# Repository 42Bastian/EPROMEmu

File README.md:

# LynxCartEmu

This repo is based on Brian's repo, see original comments below.

This fork is solely to support Atari Lynx Carts.
Upon start, the firmware loads either a `game.lnx` file or if not available provides a uBLL for Lynx.

A new ROM image can be uploaded (as .lnx file) and will be stored in internal RAM and on SD card (if available) for the next boot.

Sending is done via `SendCard.py`.

The firmware allows to "reload" the SD cart via serial command `cr` if game.lnx was saved on a PC on the card.

---

# EPROMEmu

**!! WARNING: I have no idea what I'm doing !!**

I've decided to make this public in the rare event it might help someone.

This is a very simple, likely very wrong (EP)ROM emulator using a Teensy 4.1 and Arduino/PlatformIO.  It works for my purposes (emulating an EPROM for
use in an Atari Lynx EPROM cartridge), but it it is probably not the "correct" way to design hardware.  I have also used it on Game Gear and Vectrex EPROM cartridges,
but it was not heavily tested.

Please take caution with using anything you see here.  It's my first time using KiCad, my first time designing a PCB, and my first time creating hardware.  Again,
it works for my purposes, but perhaps it'll burn your house down.

Enjoy!

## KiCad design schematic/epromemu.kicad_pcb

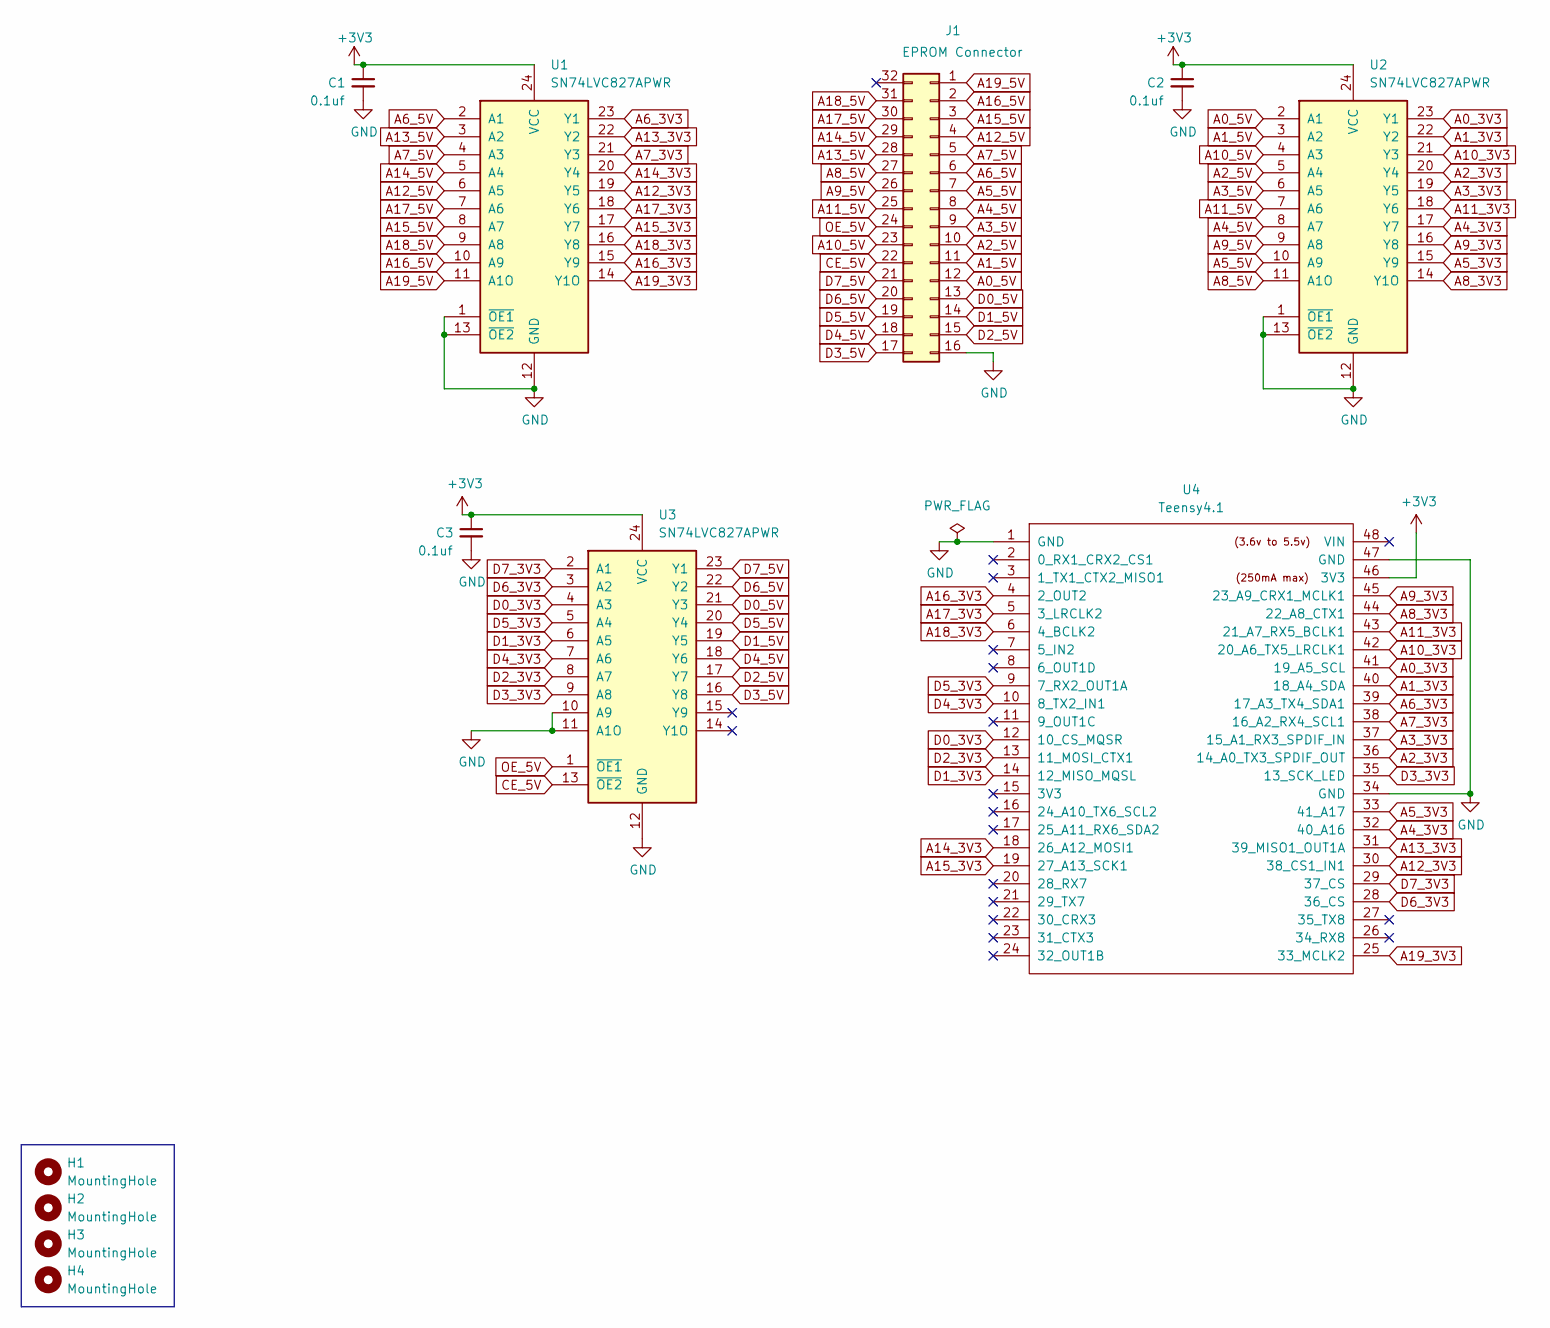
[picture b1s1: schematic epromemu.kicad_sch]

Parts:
C1, C2, C3: 0.1uf; C_0603_1608Metric_Pad1.08x0.95mm_HandSolder
H1, H2, H3, H4: MountingHole; MountingHole_2.2mm_M2_ISO7380
J1: EPROM Connector; PinHeader_2x16_P2.54mm_Vertical
U1, U2, U3: SN74LVC827APWR; SOIC-24W_7.5x15.4mm_P1.27mm
U4: Teensy4.1; Teensy41

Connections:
+3V3: C1.1, C2.1, C3.1, U1.24 (VCC), U2.24 (VCC), U3.24 (VCC), U4.46 (3V3)
A0_3V3: U2.23 (Y1), U4.41 (19_A5_SCL)
A0_5V: J1.12, U2.2 (A1)
A1_3V3: U2.22 (Y2), U4.40 (18_A4_SDA)
A1_5V: J1.11, U2.3 (A2)
A2_3V3: U2.20 (Y4), U4.36 (14_A0_TX3_SPDIF_OUT)
A2_5V: J1.10, U2.5 (A4)
A3_3V3: U2.19 (Y5), U4.37 (15_A1_RX3_SPDIF_IN)
A3_5V: J1.9, U2.6 (A5)
A4_3V3: U2.17 (Y7), U4.32 (40_A16)
A4_5V: J1.8, U2.8 (A7)
A5_3V3: U2.15 (Y9), U4.33 (41_A17)
A5_5V: J1.7, U2.10 (A9)
A6_3V3: U1.23 (Y1), U4.39 (17_A3_TX4_SDA1)
A6_5V: J1.6, U1.2 (A1)
A7_3V3: U1.21 (Y3), U4.38 (16_A2_RX4_SCL1)
A7_5V: J1.5, U1.4 (A3)
A8_3V3: U2.14 (Y1O), U4.44 (22_A8_CTX1)
A8_5V: J1.27, U2.11 (A1O)
A9_3V3: U2.16 (Y8), U4.45 (23_A9_CRX1_MCLK1)
A9_5V: J1.26, U2.9 (A8)
A10_3V3: U2.21 (Y3), U4.42 (20_A6_TX5_LRCLK1)
A10_5V: J1.23, U2.4 (A3)
A11_3V3: U2.18 (Y6), U4.43 (21_A7_RX5_BCLK1)
A11_5V: J1.25, U2.7 (A6)
A12_3V3: U1.19 (Y5), U4.30 (38_CS1_IN1)
A12_5V: J1.4, U1.6 (A5)
A13_3V3: U1.22 (Y2), U4.31 (39_MISO1_OUT1A)
A13_5V: J1.28, U1.3 (A2)
A14_3V3: U1.20 (Y4), U4.18 (26_A12_MOSI1)
A14_5V: J1.29, U1.5 (A4)
A15_3V3: U1.17 (Y7), U4.19 (27_A13_SCK1)
A15_5V: J1.3, U1.8 (A7)
A16_3V3: U1.15 (Y9), U4.4 (2_OUT2)
A16_5V: J1.2, U1.10 (A9)
A17_3V3: U1.18 (Y6), U4.5 (3_LRCLK2)
A17_5V: J1.30, U1.7 (A6)
A18_3V3: U1.16 (Y8), U4.6 (4_BCLK2)
A18_5V: J1.31, U1.9 (A8)
A19_3V3: U1.14 (Y1O), U4.25 (33_MCLK2)
A19_5V: J1.1, U1.11 (A1O)
CE_5V: J1.22, U3.13 (~OE2)
D0_3V3: U3.4 (A3), U4.12 (10_CS_MQSR)
D0_5V: J1.13, U3.21 (Y3)
D1_3V3: U3.6 (A5), U4.14 (12_MISO_MQSL)
D1_5V: J1.14, U3.19 (Y5)
D2_3V3: U3.8 (A7), U4.13 (11_MOSI_CTX1)
D2_5V: J1.15, U3.17 (Y7)
D3_3V3: U3.9 (A8), U4.35 (13_SCK_LED)
D3_5V: J1.17, U3.16 (Y8)
D4_3V3: U3.7 (A6), U4.10 (8_TX2_IN1)
D4_5V: J1.18, U3.18 (Y6)
D5_3V3: U3.5 (A4), U4.9 (7_RX2_OUT1A)
D5_5V: J1.19, U3.20 (Y4)
D6_3V3: U3.3 (A2), U4.28 (36_CS)
D6_5V: J1.20, U3.22 (Y2)
D7_3V3: U3.2 (A1), U4.29 (37_CS)
D7_5V: J1.21, U3.23 (Y1)
GND: C1.2, C2.2, C3.2, J1.16, U1.1 (~OE1), U1.12 (GND), U1.13 (~OE2), U2.1 (~OE1), U2.12 (GND), U2.13 (~OE2), U3.10 (A9), U3.11 (A1O), U3.12 (GND), U4.1 (GND), U4.34 (GND), U4.47 (GND)
OE_5V: J1.24, U3.1 (~OE1)

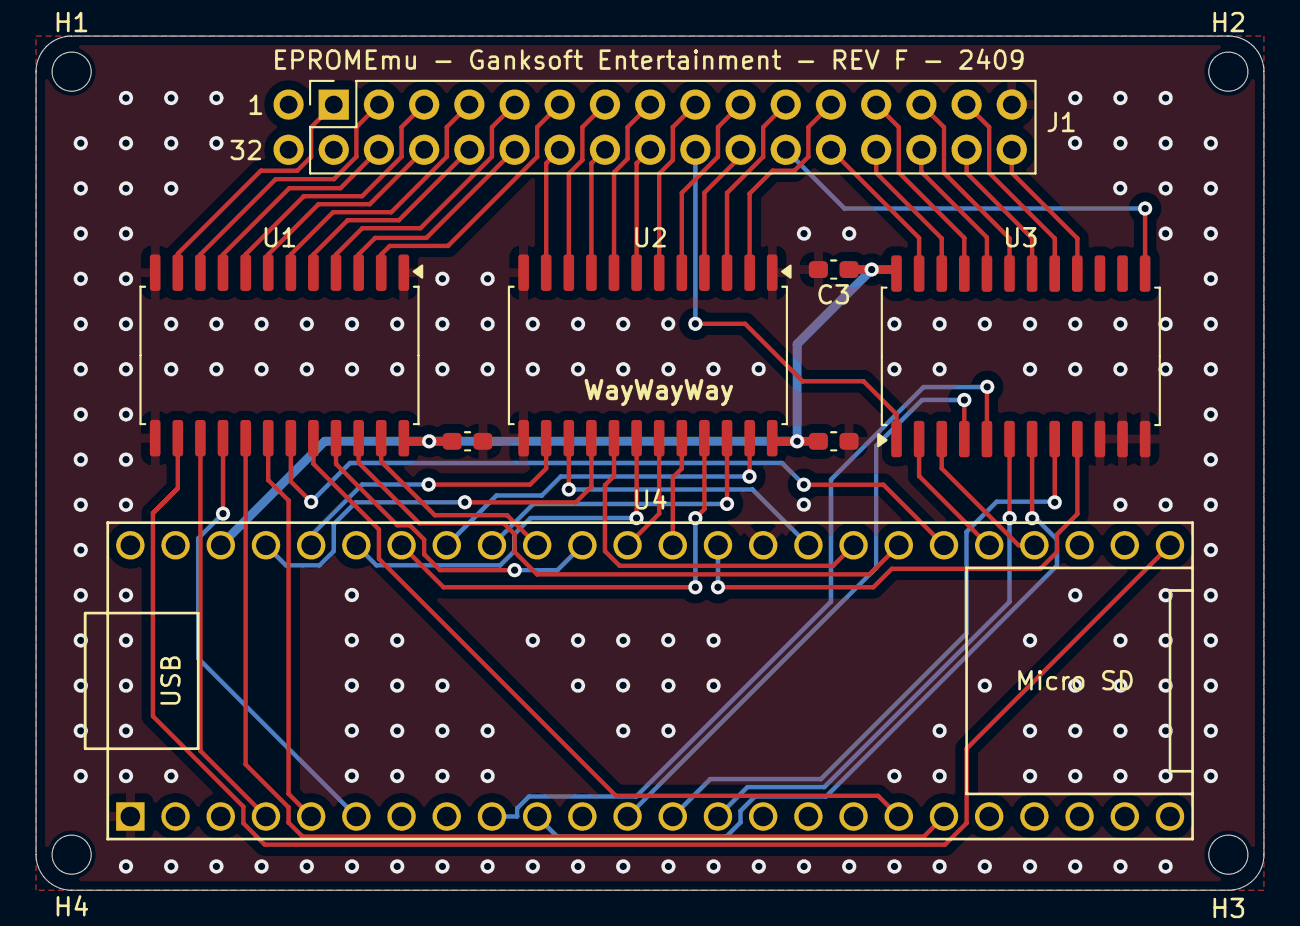
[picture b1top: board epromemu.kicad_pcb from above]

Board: 2 copper layers, 69.0 x 48.0 mm, 13 parts (1 on the bottom side), 60 nets.

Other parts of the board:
GanksoftLogo: LOGO; GanksoftLogo

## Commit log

2024-08-10 param validation
2024-08-10 rollback file
2024-08-14 v3 board, lynx support
2024-08-14 new eproms, lynx mode
2024-08-14 new eprom types, but not implemented
2024-08-14 all eprom types implemented?
2024-08-17 ditch littleFS, back to SD only ditch EXTMEM and use DMAMEM split up, but can only do 512KB now...
2024-08-18 REV D
2024-08-23 subtract skip off file size before validation
2024-08-26 tweaks
2024-09-14 REV E (unproduced)
2024-09-14 REV F
2024-12-01 holding...
2024-12-24 make Lynx default and check file size
2024-12-26 add schematic pdf
2024-12-27 local ld script
    support to load game.lnx file
    automatic EPROM type on size
2024-12-27 use in-built uBLL if no game.lnx is on SD or no SD found
2024-12-27 Add Command CR to reload SD card
2024-12-30 Sending .lnx works, clean up needed
2024-12-30 cleaning
2024-12-30 renamed to use Cart not Card
2024-12-30 add (c) notice
